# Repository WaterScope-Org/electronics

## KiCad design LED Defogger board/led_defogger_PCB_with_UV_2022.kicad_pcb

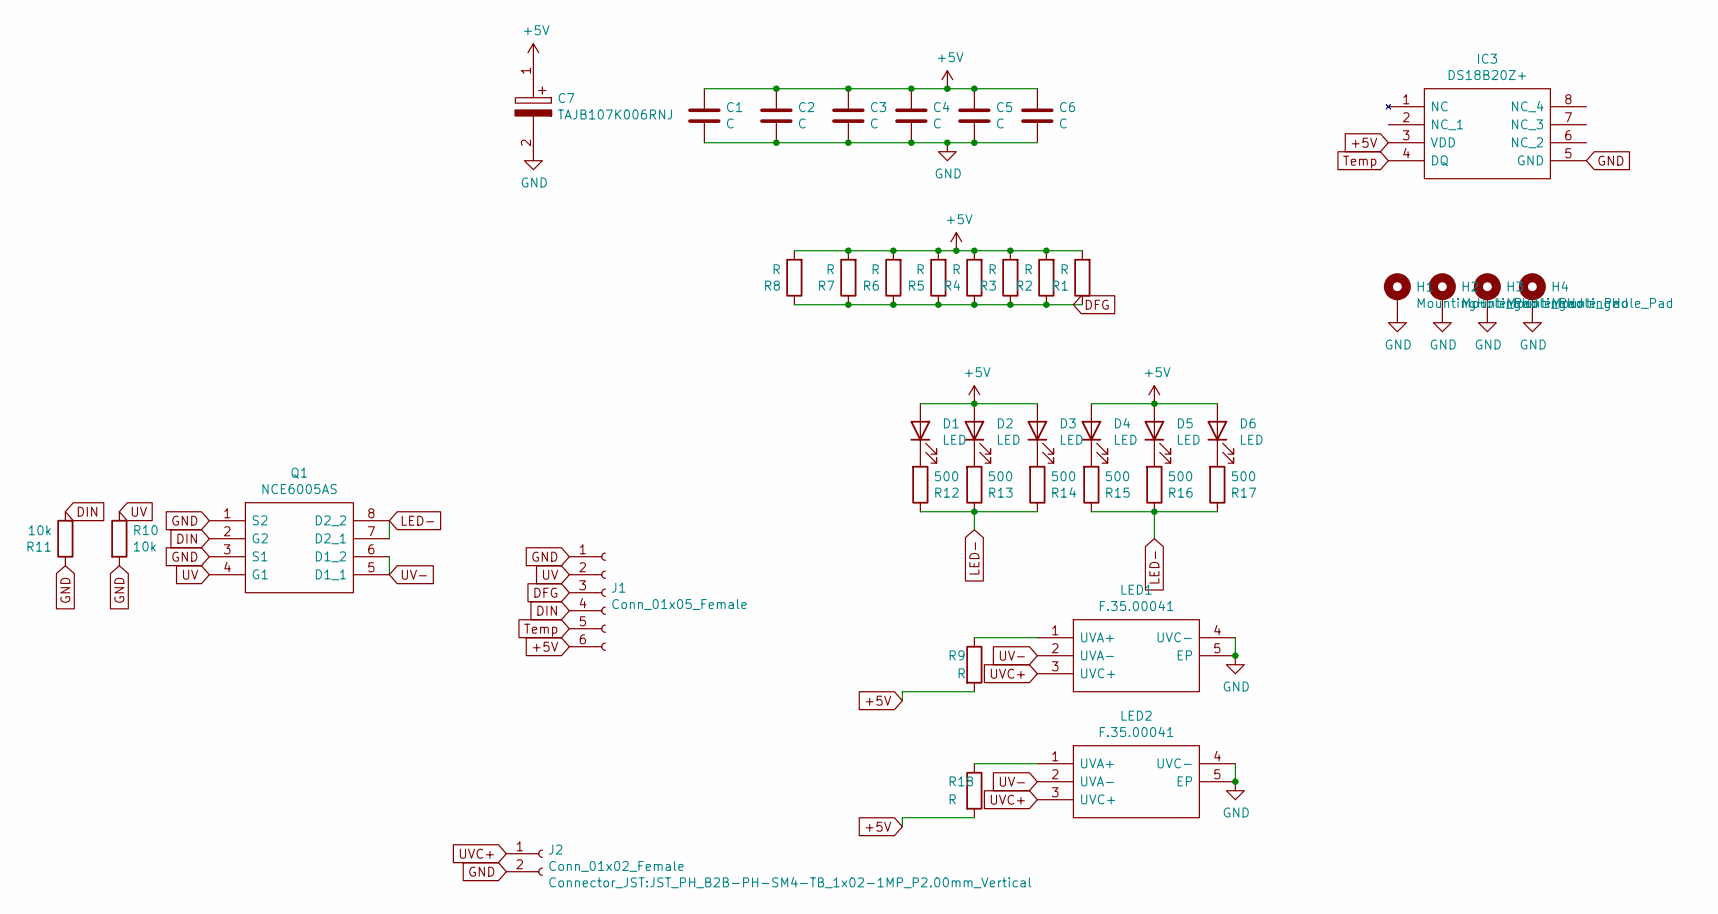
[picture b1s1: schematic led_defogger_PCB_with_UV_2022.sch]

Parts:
C1, C2, C3, C4, C5, C6: C; C_0805_2012Metric_Pad1.15x1.40mm_HandSolder
C7: TAJB107K006RNJ; CAPPM3528X210N; Manufacturer_Part_Number TAJB107K006RNJ; Mouser Part Number 581-TAJB107K006R
D1, D2, D3, D4, D5, D6: LED; LED_0603_1608Metric_Pad1.05x0.95mm_HandSolder
H1, H2, H3, H4: MountingHole_Pad; MountingHole_2.2mm_M2_DIN965_Pad
IC3: DS18B20Z+; SOIC127P600X175-8N; Manufacturer_Part_Number DS18B20Z+
J1: Conn_01x05_Female; JST_PH_B6B-PH-SM4-TB_1x06-1MP_P2.00mm_Vertical
J2: Conn_01x02_Female; JST_PH_B2B-PH-SM4-TB_1x02-1MP_P2.00mm_Vertical
LED1, LED2: F.35.00041; F3500041; Manufacturer_Part_Number F.35.00041
Q1: NCE6005AS; SOIC127P600X175-8N; Manufacturer_Part_Number NCE6005AS
R1, R2, R3, R4, R5, R6, R7, R8: R; R_1210_3225Metric_Pad1.42x2.65mm_HandSolder
R9, R18: R; R_1206_3216Metric_Pad1.30x1.75mm_HandSolder
R10, R11: 10k; R_0805_2012Metric_Pad1.15x1.40mm_HandSolder
R12, R13, R14, R15, R16, R17: 500; R_0805_2012Metric_Pad1.15x1.40mm_HandSolder

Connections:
+5V: C1.1, C2.1, C3.1, C4.1, C5.1, C6.1, C7.1, D1.2 (A), D2.2 (A), D3.2 (A), D4.2 (A), D5.2 (A), D6.2 (A), IC3.3 (VDD), J1.6, R1.2, R2.2, R3.2, R4.2, R5.2, R6.2, R7.2, R8.2, R9.2, R18.2
DFG: J1.3, R1.1, R2.1, R3.1, R4.1, R5.1, R6.1, R7.1, R8.1
DIN: J1.4, Q1.2 (G2), R11.2
GND: C1.2, C2.2, C3.2, C4.2, C5.2, C6.2, C7.2, H1.1, H2.1, H3.1, H4.1, IC3.5 (GND), J1.1, J2.2, LED1.4 (UVC-), LED1.5 (EP), LED2.4 (UVC-), LED2.5 (EP), Q1.1 (S2), Q1.3 (S1), R10.2, R11.1
LED-: Q1.7 (D2_1), Q1.8 (D2_2), R12.1, R13.1, R14.1, R15.1, R16.1, R17.1
unnamed: D1.1 (K), R12.2
unnamed: D2.1 (K), R13.2
unnamed: D3.1 (K), R14.2
unnamed: D4.1 (K), R15.2
unnamed: D5.1 (K), R16.2
unnamed: D6.1 (K), R17.2
unnamed: LED1.1 (UVA+), R9.1
unnamed: LED2.1 (UVA+), R18.1
Temp: IC3.4 (DQ), J1.5
UV: J1.2, Q1.4 (G1), R10.1
UV-: LED1.2 (UVA-), LED2.2 (UVA-), Q1.5 (D1_1), Q1.6 (D1_2)
UVC+: J2.1, LED1.3 (UVC+), LED2.3 (UVC+)

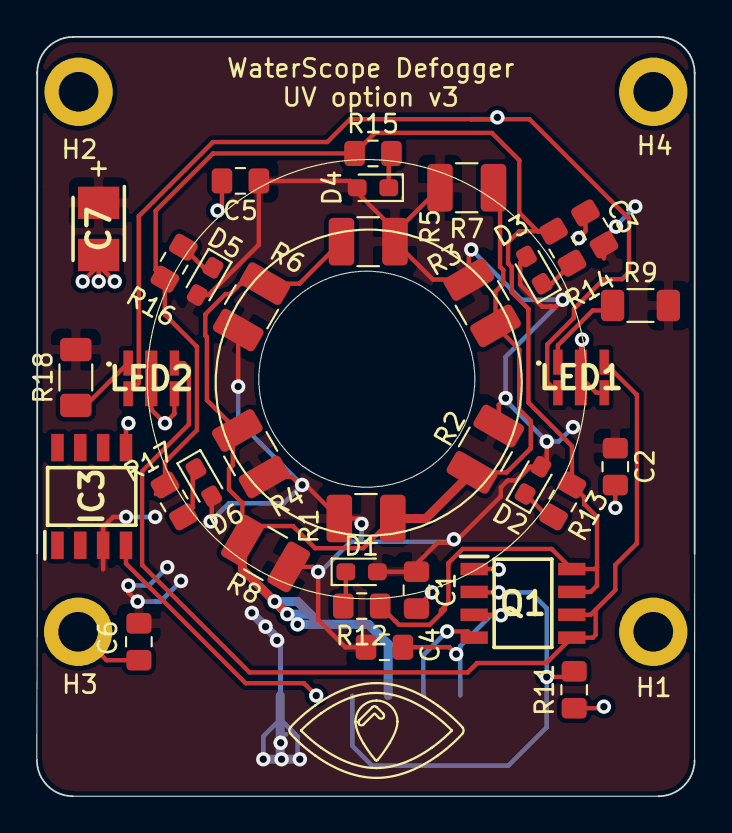
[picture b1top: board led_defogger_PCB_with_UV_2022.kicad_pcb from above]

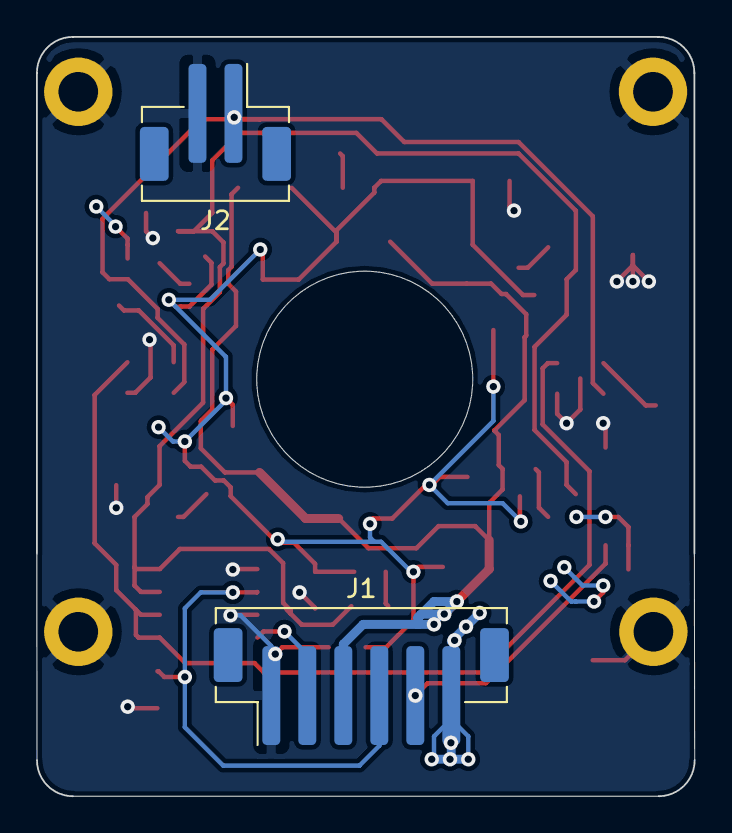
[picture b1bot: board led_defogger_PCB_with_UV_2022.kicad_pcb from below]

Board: 2 copper layers, 36.5 x 42.2 mm, 40 parts (2 on the bottom side), 17 nets.

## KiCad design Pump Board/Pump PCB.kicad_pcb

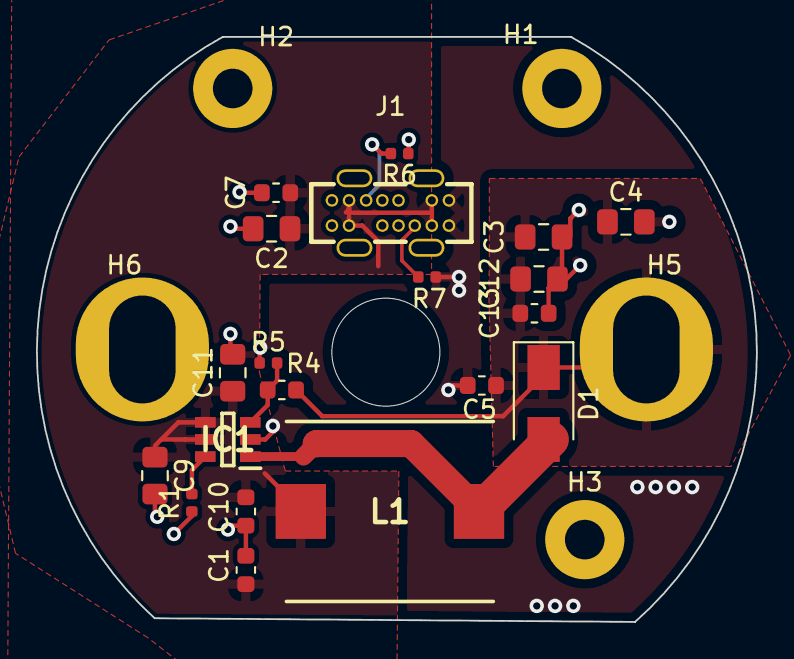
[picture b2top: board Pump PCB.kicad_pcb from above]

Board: 2 copper layers, 40.0 x 32.5 mm, 25 parts (0 on the bottom side), 8 nets.

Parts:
C1, C5, C7, C10, C13: 0.1uF; C_0603_1608Metric
C2, C3, C4, C9, C11, C12: 20uF; C_0805_2012Metric_Pad1.15x1.40mm_HandSolder
D1: D_Schottky; D_SMA
H1, H2, H3: MountingHole; MountingHole_2.2mm_M2_Pad
H5, H6: MountingHole_Pad; MountingHole_3.7mm_Pad
IC1: FP6291; SOT95P280X145-6N
J1: USB-C-TH_TYPE-C-USB-14P
L1: SMMS1040-3R3M; INDPM115100X400N
R1, R5: 10K; R_0402_1005Metric
R4: 190K; R_0603_1608Metric
R6: 5.1k; R_0402_1005Metric
R7: 5.1K; R_0402_1005Metric

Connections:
5V: C1.1, C2.1, C7.1, C9.1, C10.1, C11.1, IC1.4, IC1.5, J1.2, J1.6, J1.9, J1.13, L1.1
12V: C3.1, C4.1, C5.1, C12.1, C13.1, D1.1, H5.1, R4.2
GND: C1.2, C2.2, C3.2, C4.2, C5.2, C7.2, C9.2, C10.2, C11.2, C12.2, C13.2, H6.1, IC1.2, J1.1, J1.7, J1.8, J1.14, R1.2, R5.1, R6.1, R7.2
unnamed: D1.2, IC1.1, L1.2
unnamed: IC1.3, R4.1, R5.2
unnamed: IC1.6, R1.1
unnamed: J1.5, R7.1
unnamed: J1.12, R6.2

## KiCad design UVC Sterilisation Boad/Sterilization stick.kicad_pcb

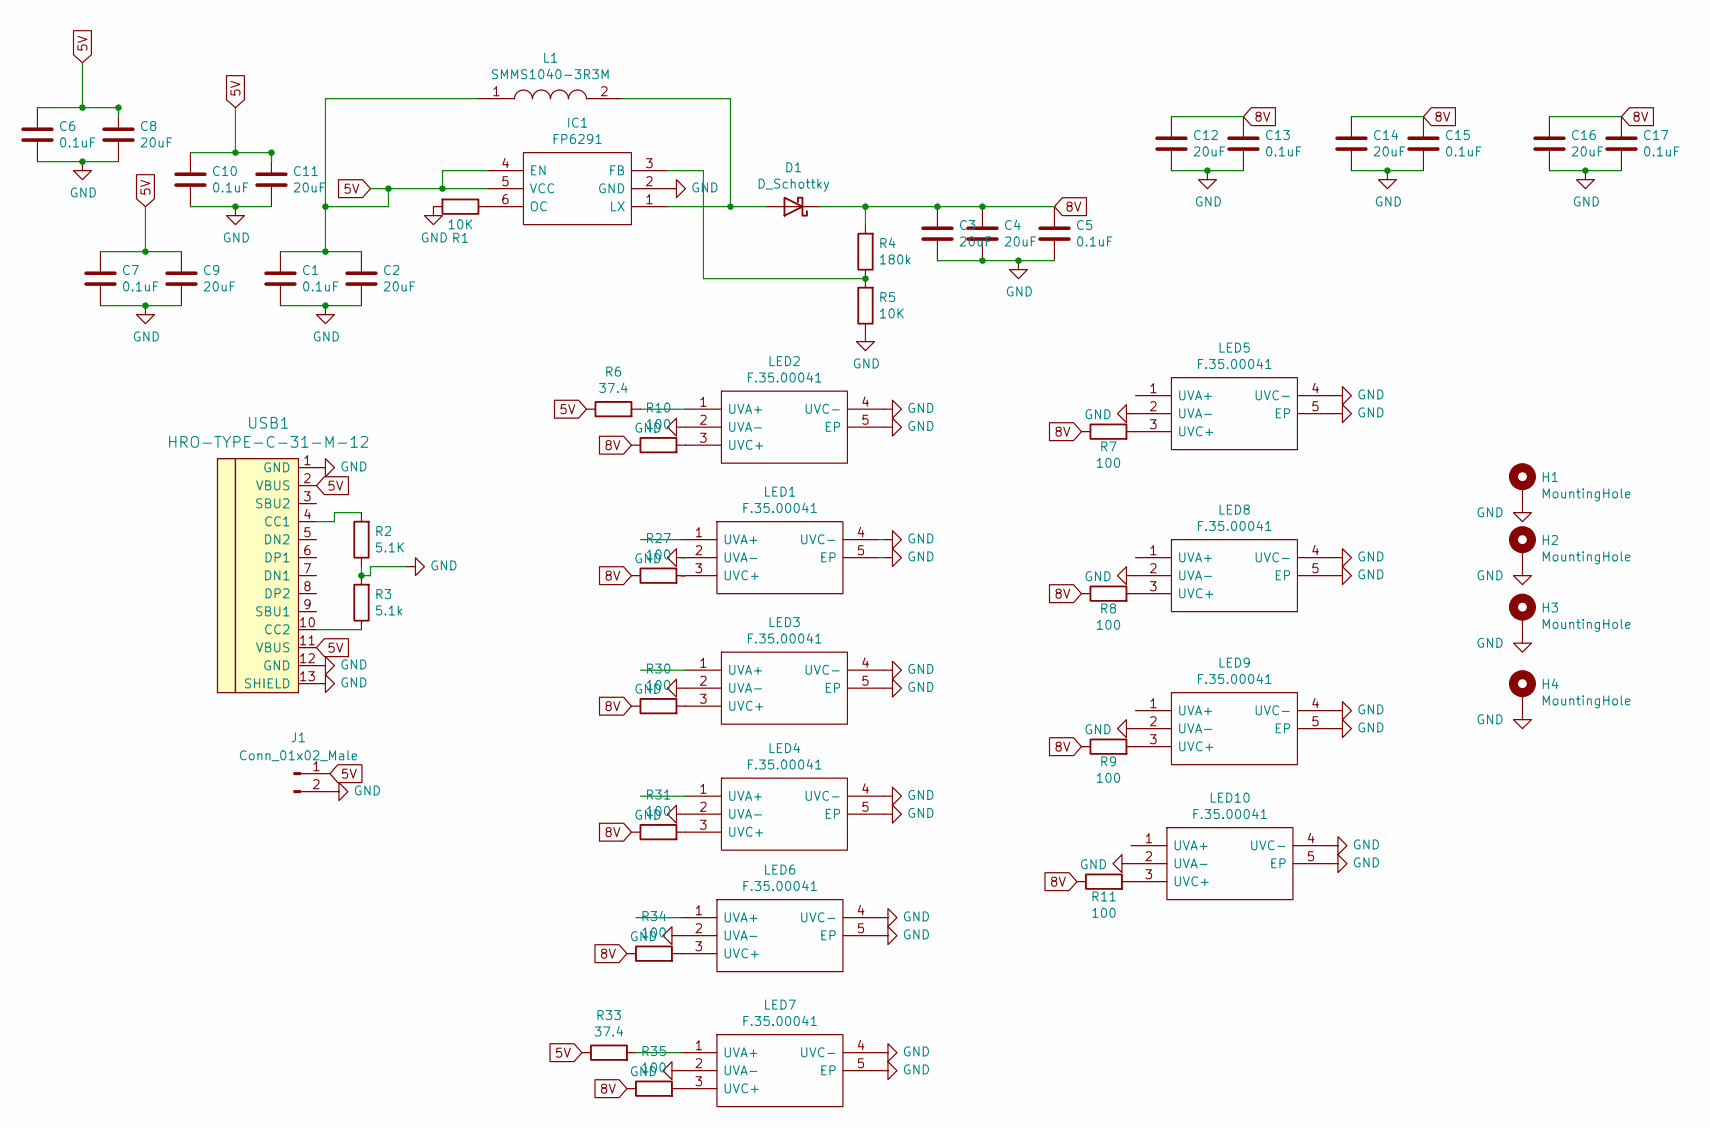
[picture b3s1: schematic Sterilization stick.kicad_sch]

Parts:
C1, C5, C6, C7, C10, C13, C15, C17: 0.1uF; C_0603_1608Metric; LCSC Part C14663
C2, C3, C4, C8, C9, C11, C12, C14, C16: 20uF; C_0805_2012Metric_Pad1.15x1.40mm_HandSolder; LCSC Part C45783
D1: D_Schottky; D_SMA; LCSC Part C383313
H1, H2, H3, H4: MountingHole; MountingHole_4.3mm_M4_DIN965_Pad
IC1: FP6291; SOT95P280X145-6N; Manufacturer_Part_Number FP6291; LCSC Part C18701
J1: Conn_01x02_Male; JST_XH_S2B-XH-A-1_1x02_P2.50mm_Horizontal
L1: SMMS1040-3R3M; INDPM115100X400N; Manufacturer_Part_Number SMMS1040-3R3M; LCSC Part C149592
LED1, LED2, LED3, LED4, LED5, LED6, LED7, LED8, LED9, LED10: F.35.00041; F3500041; Manufacturer_Part_Number F.35.00041; LCSC Part C909692
R1: 10K; R_0402_1005Metric; LCSC Part C25744
R2: 5.1K; R_0402_1005Metric; LCSC Part C25905
R3: 5.1k; R_0402_1005Metric; LCSC Part C25905
R4: 180k; R_0603_1608Metric; LCSC Part C22932
R5: 10K; R_0603_1608Metric_Pad0.98x0.95mm_HandSolder; LCSC Part C25744
R6, R33: 37.4; R_1206_3216Metric; LCSC Part C247280
R7, R8, R9, R10, R11, R27, R30, R31, R34, R35: 100; R_1206_3216Metric; LCSC Part C17901
USB1: HRO-TYPE-C-31-M-12; HRO-TYPE-C-31-M-12-HandSoldering

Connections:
5V: C1.1, C2.1, C6.1, C7.1, C8.1, C9.1, C10.1, C11.1, IC1.4 (EN), IC1.5 (VCC), J1.1, L1.1, R6.1, R33.1, USB1.2 (VBUS), USB1.11 (VBUS)
8V: C3.1, C4.1, C5.1, C12.1, C13.1, C14.1, C15.1, C16.1, C17.1, D1.1 (K), R4.2, R7.1, R8.1, R9.1, R10.1, R11.1, R27.1, R30.1, R31.1, R34.1, R35.1
GND: C1.2, C2.2, C3.2, C4.2, C5.2, C6.2, C7.2, C8.2, C9.2, C10.2, C11.2, C12.2, C13.2, C14.2, C15.2, C16.2, C17.2, H1.1, H2.1, H3.1, H4.1, IC1.2 (GND), J1.2, LED1.2 (UVA-), LED1.4 (UVC-), LED1.5 (EP), LED2.2 (UVA-), LED2.4 (UVC-), LED2.5 (EP), LED3.2 (UVA-), LED3.4 (UVC-), LED3.5 (EP), LED4.2 (UVA-), LED4.4 (UVC-), LED4.5 (EP), LED5.2 (UVA-), LED5.4 (UVC-), LED5.5 (EP), LED6.2 (UVA-), LED6.4 (UVC-), LED6.5 (EP), LED7.2 (UVA-), LED7.4 (UVC-), LED7.5 (EP), LED8.2 (UVA-), LED8.4 (UVC-), LED8.5 (EP), LED9.2 (UVA-), LED9.4 (UVC-), LED9.5 (EP), LED10.2 (UVA-), LED10.4 (UVC-), LED10.5 (EP), R1.2, R2.1, R3.2, R5.1, USB1.1 (GND), USB1.12 (GND), USB1.13 (SHIELD)
unnamed: D1.2 (A), IC1.1 (LX), L1.2
unnamed: IC1.3 (FB), R4.1, R5.2
unnamed: IC1.6 (OC), R1.1
unnamed: LED1.3 (UVC+), R27.2
unnamed: LED2.1 (UVA+), R6.2
unnamed: LED2.3 (UVC+), R10.2
unnamed: LED3.3 (UVC+), R30.2
unnamed: LED4.3 (UVC+), R31.2
unnamed: LED5.3 (UVC+), R7.2
unnamed: LED6.3 (UVC+), R34.2
unnamed: LED7.1 (UVA+), R33.2
unnamed: LED7.3 (UVC+), R35.2
unnamed: LED8.3 (UVC+), R8.2
unnamed: LED9.3 (UVC+), R9.2
unnamed: LED10.3 (UVC+), R11.2
unnamed: R2.2, USB1.4 (CC1)
unnamed: R3.1, USB1.10 (CC2)

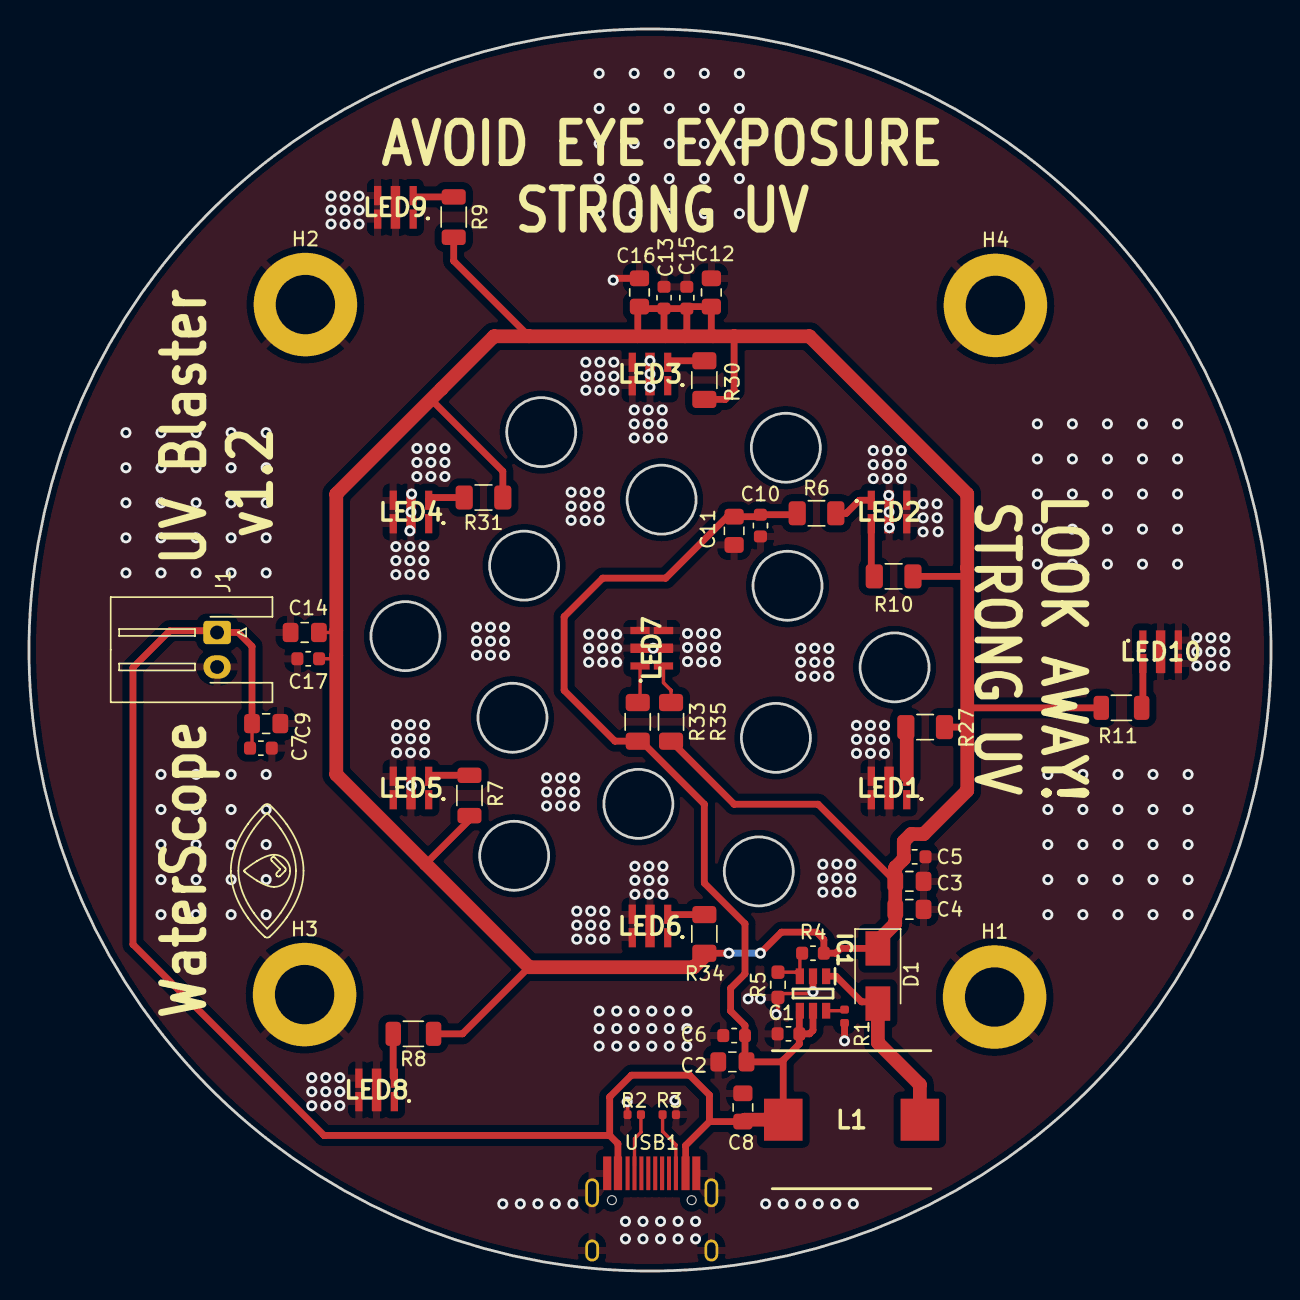
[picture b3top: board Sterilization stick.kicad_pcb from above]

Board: 2 copper layers, 90.0 x 90.0 mm, 53 parts (0 on the bottom side), 20 nets.

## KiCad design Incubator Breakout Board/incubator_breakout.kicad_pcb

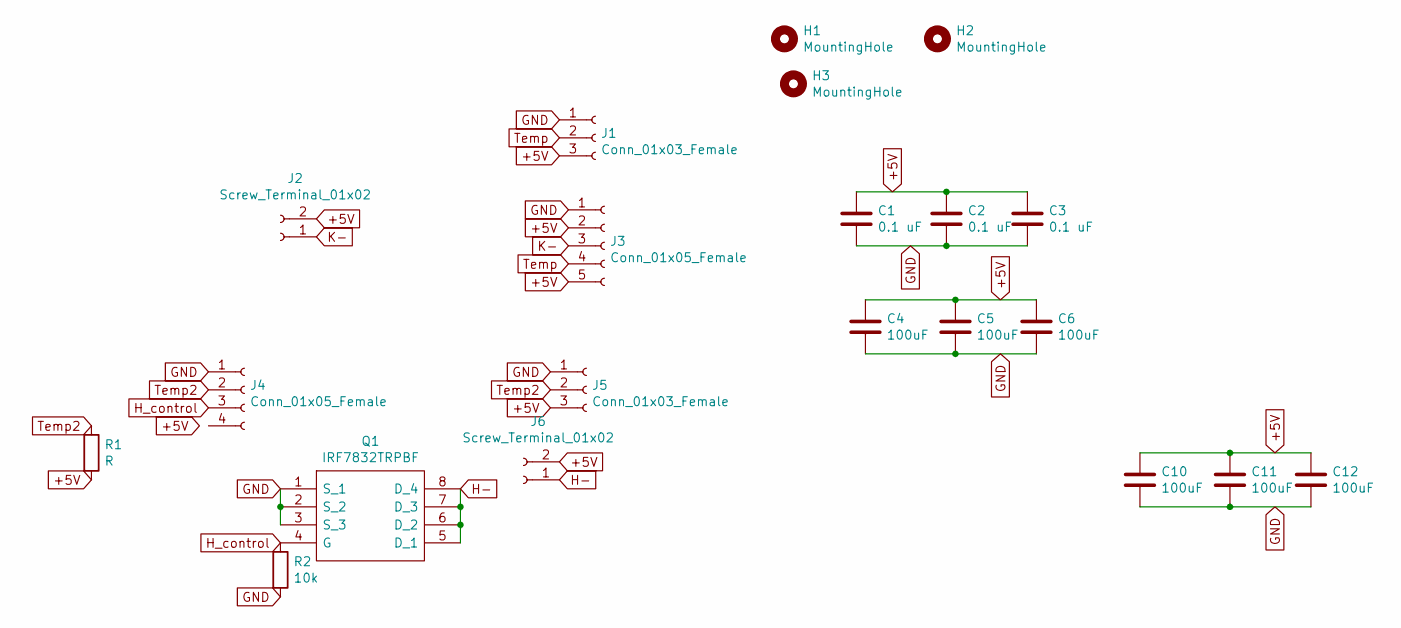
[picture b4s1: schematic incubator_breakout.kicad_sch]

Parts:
C1, C2, C3: 0.1 uF; C_0805_2012Metric_Pad1.15x1.40mm_HandSolder
C4, C5, C6: 100uF; C_0805_2012Metric_Pad1.15x1.40mm_HandSolder
C10, C11, C12: 100uF; C_0805_2012Metric_Pad1.18x1.45mm_HandSolder
H1, H2, H3: MountingHole; MountingHole_2.2mm_M2_Pad
J1, J5: Conn_01x03_Female; JST_PH_S3B-PH-K_1x03_P2.00mm_Horizontal
J2, J6: Screw_Terminal_01x02; JST_XH_S2B-XH-A_1x02_P2.50mm_Horizontal
J3: Conn_01x05_Female; JST_PH_S5B-PH-K_1x05_P2.00mm_Horizontal
J4: Conn_01x05_Female; JST_PH_S4B-PH-K_1x04_P2.00mm_Horizontal
Q1: IRF7832TRPBF; SOIC127P600X175-8N; Manufacturer_Part_Number NTMS4807NR2G; Mouser Part Number 863-NTMS4807NR2G
R1: R; R_0402_1005Metric
R2: 10k; R_0805_2012Metric_Pad1.15x1.40mm_HandSolder

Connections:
+5V: C1.1, C2.1, C3.1, C4.1, C5.1, C6.1, C10.1, C11.1, C12.1, J1.3, J2.2, J3.2, J3.5, J5.3, J6.2, R1.2
GND: C1.2, C2.2, C3.2, C4.2, C5.2, C6.2, C10.2, C11.2, C12.2, J1.1, J3.1, J4.1, J5.1, Q1.1 (S_1), Q1.2 (S_2), Q1.3 (S_3), R2.2
H-: J6.1, Q1.5 (D_1), Q1.6 (D_2), Q1.7 (D_3), Q1.8 (D_4)
H_control: J4.3, Q1.4 (G), R2.1
K-: J2.1, J3.3
Temp: J1.2, J3.4
Temp2: J4.2, J5.2, R1.1

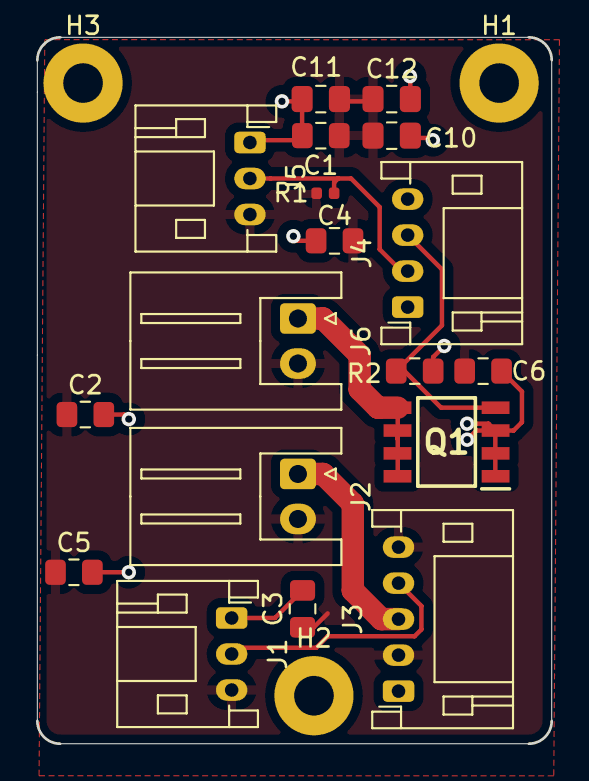
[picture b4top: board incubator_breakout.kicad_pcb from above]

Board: 2 copper layers, 28.6 x 39.2 mm, 21 parts (0 on the bottom side), 7 nets.

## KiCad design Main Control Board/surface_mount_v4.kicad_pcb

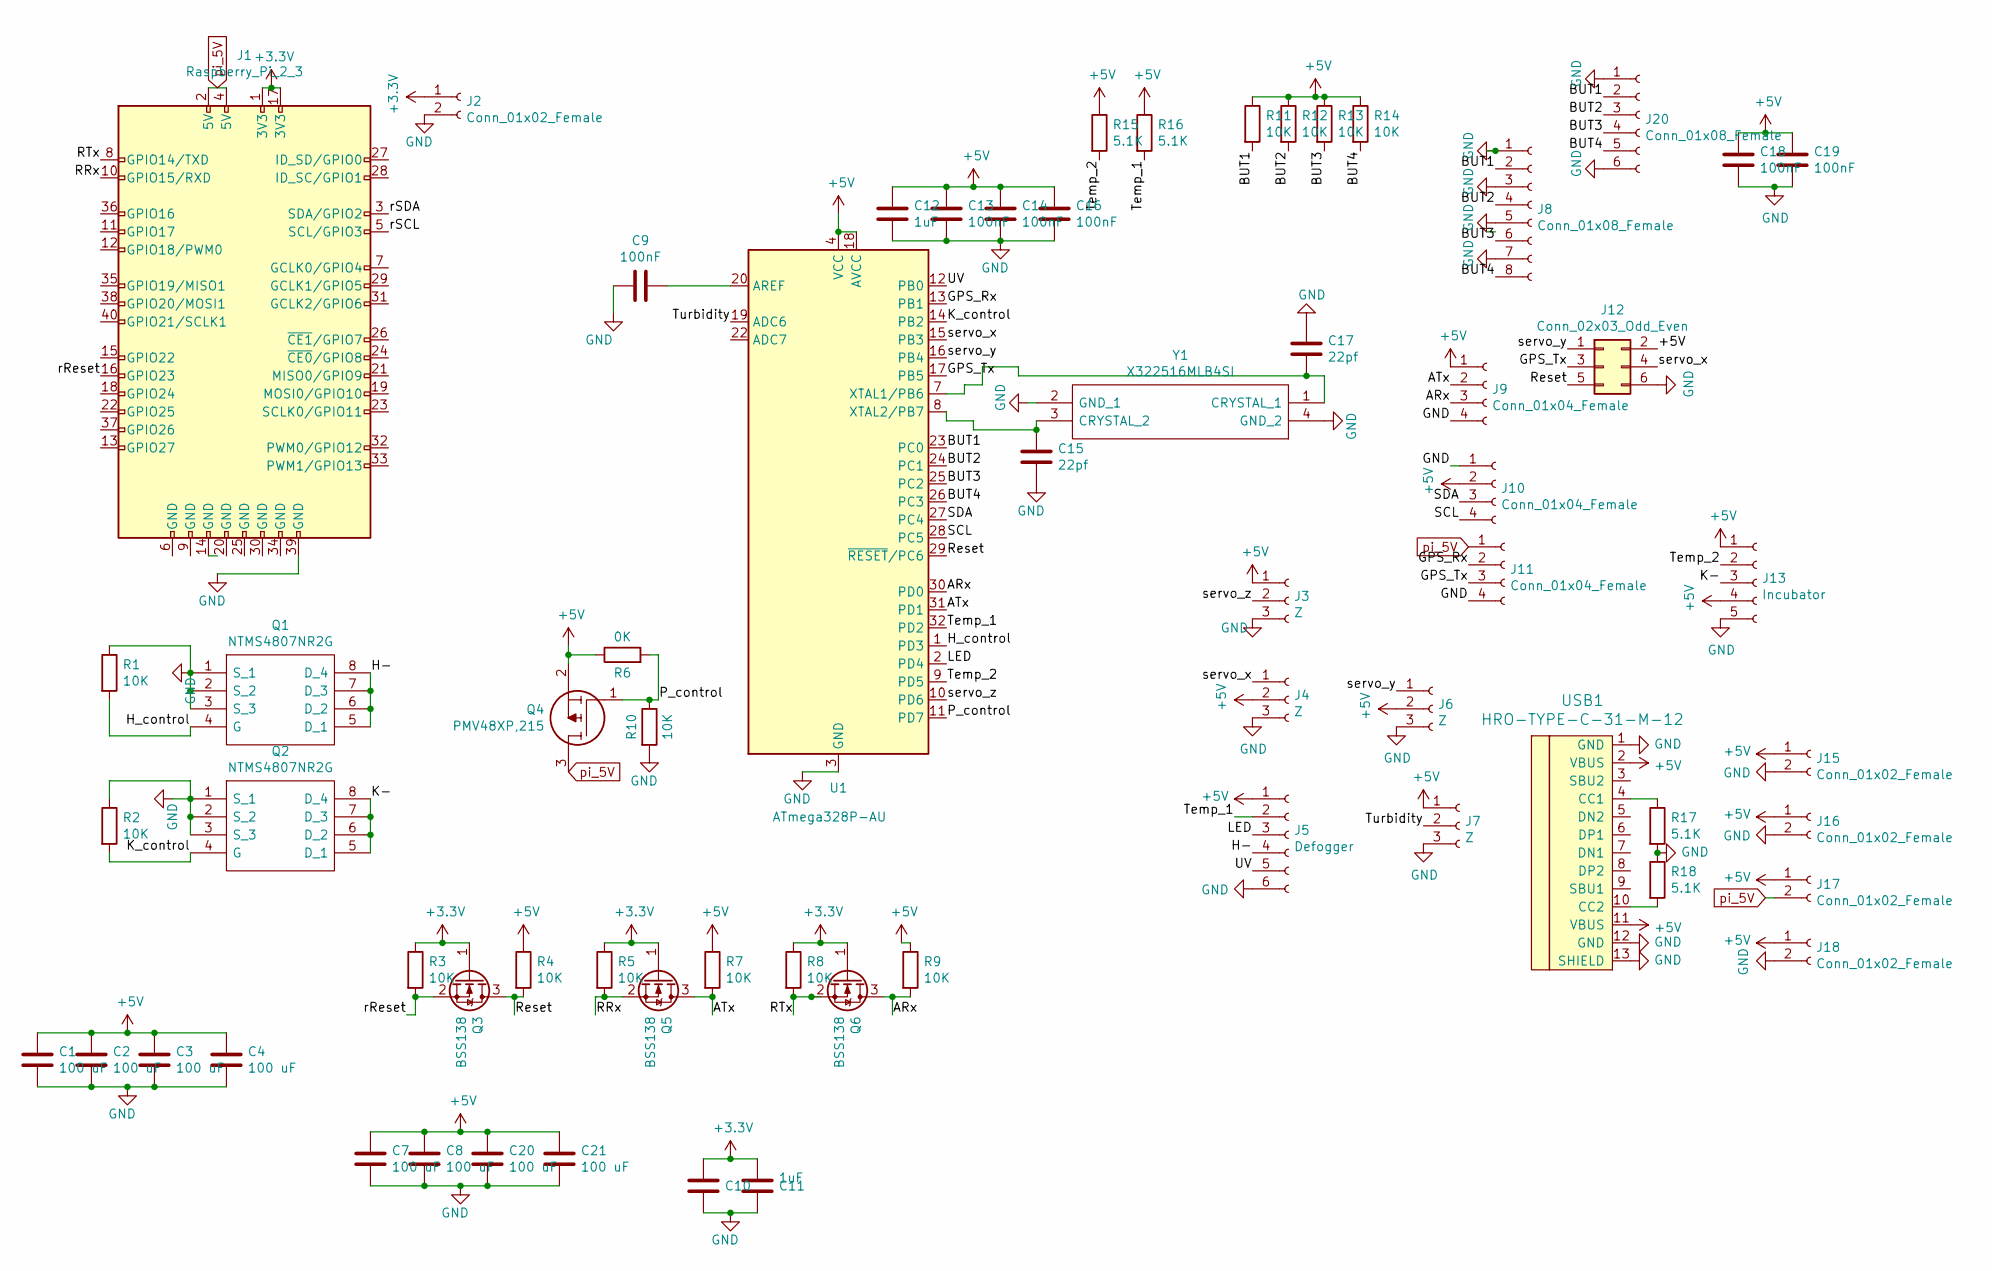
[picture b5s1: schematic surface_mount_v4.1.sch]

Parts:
C1, C2, C3, C4, C7, C8, C20, C21: 100 uF; R_1206_3216Metric; LCSC Part C15008
C9, C10, C13, C14, C16, C18, C19: 100nF; C_0603_1608Metric
C11, C12: 1uF; C_0603_1608Metric
C15, C17: 22pf; C_0603_1608Metric_Pad1.05x0.95mm_HandSolder; LCSC Part C1653
J1: Raspberry_Pi_2_3; PinSocket_2x20_P2.54mm_Vertical_SMD
J2, J17: Conn_01x02_Female; PinHeader_1x02_P2.54mm_Vertical
J3, J7: Z; JST_PH_B3B-PH-SM4-TB_1x03-1MP_P2.00mm_Vertical
J4, J6: Z; PinHeader_1x03_P2.54mm_Vertical
J5: Defogger; JST_PH_S6B-PH-SM4-TB_1x06-1MP_P2.00mm_Horizontal
J8: Conn_01x08_Female; JST_PH_S8B-PH-SM4-TB_1x08-1MP_P2.00mm_Horizontal
J9: Conn_01x04_Female; PinHeader_1x04_P2.54mm_Vertical
J10, J11: Conn_01x04_Female; JST_PH_B4B-PH-SM4-TB_1x04-1MP_P2.00mm_Vertical
J12: Conn_02x03_Odd_Even; PinHeader_2x03_P2.54mm_Vertical
J13: Incubator; JST_PH_S5B-PH-SM4-TB_1x05-1MP_P2.00mm_Horizontal
J15, J16, J18: Conn_01x02_Female; JST_XH_B2B-XH-A_1x02_P2.50mm_Vertical
J20: Conn_01x08_Female; 06FEBTVKN
Q1, Q2: NTMS4807NR2G; SOIC127P600X175-8N; Manufacturer_Part_Number NTMS4807NR2G; Mouser Part Number 863-NTMS4807NR2G
Q3, Q5, Q6: BSS138; SOT-23
Q4: PMV48XP,215; SOT95P230X110-3N; Manufacturer_Part_Number PMV48XP,215; Mouser Part Number 771-PMV48XP215
R1, R2, R3, R4, R5, R7, R8, R9, R10, R11, R12, R13, R14: 10K; R_0402_1005Metric
R6: 0K; R_0805_2012Metric_Pad1.15x1.40mm_HandSolder
R15, R16, R17, R18: 5.1K; R_0402_1005Metric
U1: ATmega328P-AU; TQFP-32_7x7mm_P0.8mm
USB1: HRO-TYPE-C-31-M-12; HRO-TYPE-C-31-M-12-Assembly
Y1: X322516MLB4SI; Manufacturer_Part_Number X322516MLB4SI

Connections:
+3V3: C10.1, C11.2, J1.1 (3V3), J1.17 (3V3), J2.1, Q3.1 (G), Q5.1 (G), Q6.1 (G), R3.1, R5.1, R8.1
+5V: C1.1, C2.1, C3.1, C4.1, C7.1, C8.1, C12.1, C13.1, C14.1, C16.1, C18.1, C19.1, C20.1, C21.1, J3.1, J4.2, J5.1, J6.2, J7.1, J9.1, J10.2, J12.2, J13.1, J13.4, J15.1, J16.1, J17.1, J18.1, Q4.2, R4.1, R6.1, R7.1, R9.1, R11.1, R12.1, R13.1, R14.1, R15.1, R16.1, U1.4 (VCC), U1.6 (VCC), U1.18 (AVCC), USB1.2 (VBUS), USB1.11 (VBUS)
/ARx: J9.3, Q6.3 (D), R9.2, U1.30 (PD0)
/ATx: J9.2, Q5.3 (D), R7.2, U1.31 (PD1)
/BUT1: J8.2, J20.2, R11.2, U1.23 (PC0)
/BUT2: J8.4, J20.3, R12.2, U1.24 (PC1)
/BUT3: J8.6, J20.4, R13.2, U1.25 (PC2)
/BUT4: J8.8, J20.5, R14.2, U1.26 (PC3)
/GPS_Rx: J11.2, U1.13 (PB1)
/GPS_Tx: J11.3, J12.3, U1.17 (PB5)
/H-: J5.4, Q1.5 (D_1), Q1.6 (D_2), Q1.7 (D_3), Q1.8 (D_4)
/H_control: Q1.4 (G), R1.2, U1.1 (PD3)
/K-: J13.3, Q2.5 (D_1), Q2.6 (D_2), Q2.7 (D_3), Q2.8 (D_4)
/K_control: Q2.4 (G), R2.2, U1.14 (PB2)
/LED: J5.3, U1.2 (PD4)
/P_control: Q4.1, R6.2, R10.1, U1.11 (PD7)
/RRx: J1.10 (GPIO15/RXD), Q5.2 (S), R5.2
/RTx: J1.8 (GPIO14/TXD), Q6.2 (S), R8.2
/Reset: J12.5, Q3.3 (D), R4.2, U1.29 (~RESET~/PC6)
/SCL: J10.4, U1.28 (PC5)
/SDA: J10.3, U1.27 (PC4)
/Temp_1: J5.2, R16.2, U1.32 (PD2)
/Temp_2: J13.2, R15.2, U1.9 (PD5)
/Turbidity: J7.2, U1.19 (ADC6)
/UV: J5.5, U1.12 (PB0)
/rReset: J1.16 (GPIO23), Q3.2 (S), R3.2
/rSCL: J1.5 (SCL/GPIO3)
/rSDA: J1.3 (SDA/GPIO2)
/servo_x: J4.1, J12.4, U1.15 (PB3)
/servo_y: J6.1, J12.1, U1.16 (PB4)
/servo_z: J3.2, U1.10 (PD6)
GND: C1.2, C2.2, C3.2, C4.2, C7.2, C8.2, C9.2, C10.2, C11.1, C12.2, C13.2, C14.2, C15.2, C16.2, C17.1, C18.2, C19.2, C20.2, C21.2, J1.39 (GND), J2.2, J3.3, J4.3, J5.6, J6.3, J7.3, J8.1, J8.3, J8.5, J8.7, J9.4, J10.1, J11.4, J12.6, J13.5, J15.2, J16.2, J18.2, J20.1, J20.6, Q1.1 (S_1), Q1.2 (S_2), Q1.3 (S_3), Q2.1 (S_1), Q2.2 (S_2), Q2.3 (S_3), R1.1, R2.1, R10.2, R17.2, R18.1, U1.3 (GND), U1.5 (GND), U1.21 (GND), USB1.1 (GND), USB1.12 (GND), USB1.13 (SHIELD), Y1.2 (GND_1), Y1.4 (GND_2)
unnamed: C9.1, U1.20 (AREF)
unnamed: C15.1, U1.8 (XTAL2/PB7), Y1.3 (CRYSTAL_2)
unnamed: C17.2, U1.7 (XTAL1/PB6), Y1.1 (CRYSTAL_1)
unnamed: R17.1, USB1.4 (CC1)
unnamed: R18.2, USB1.10 (CC2)
pi_5V: J1.2 (5V), J1.4 (5V), J11.1, J17.2, Q4.3

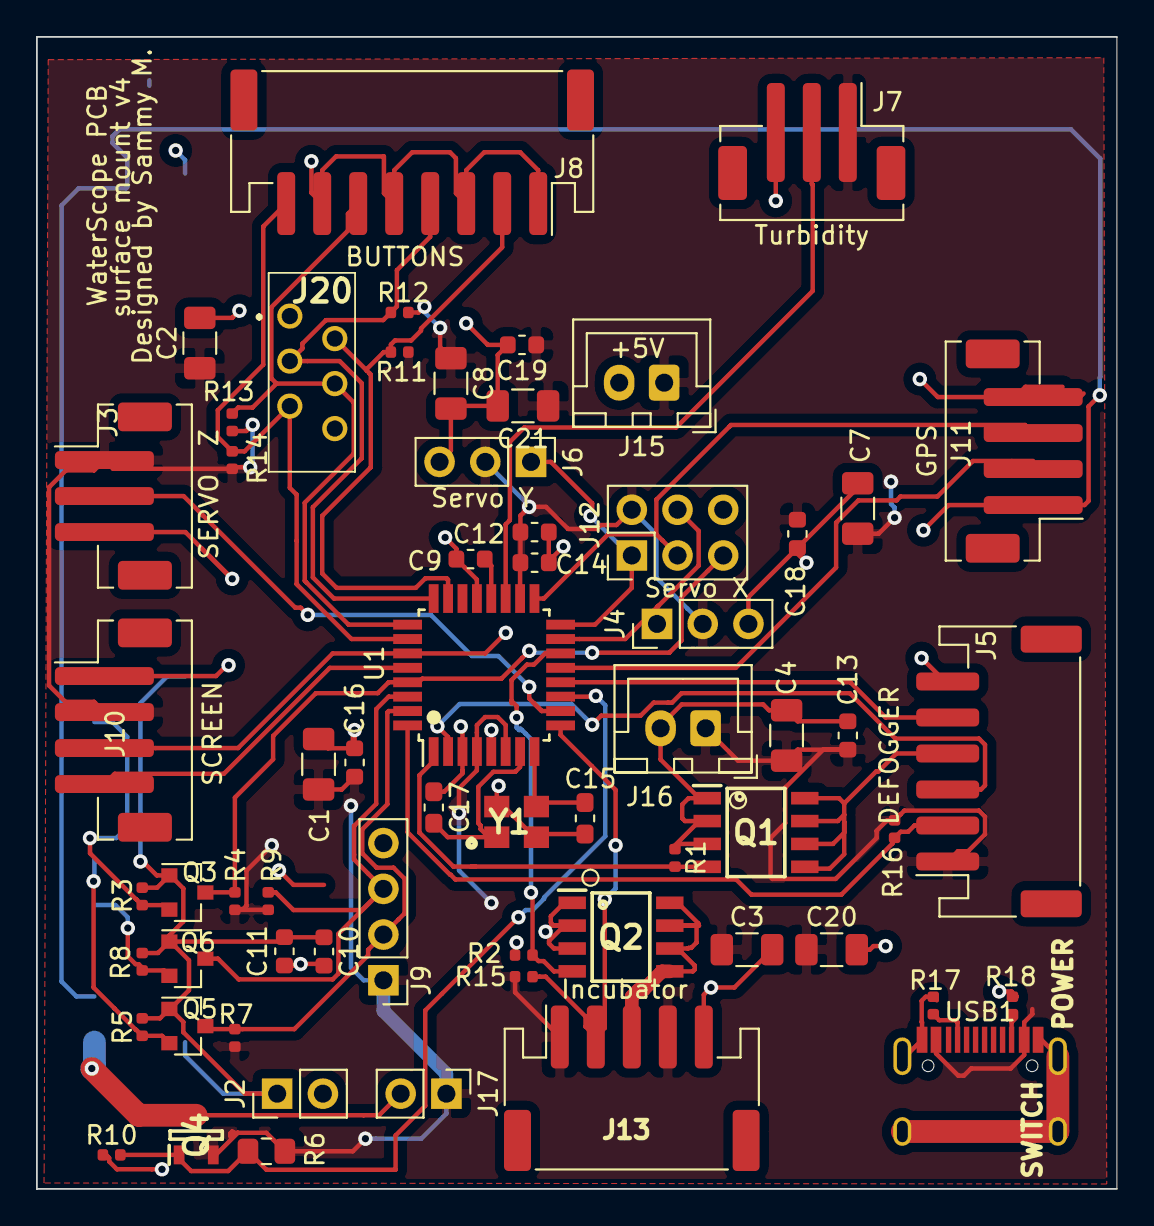
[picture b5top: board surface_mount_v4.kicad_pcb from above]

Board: 2 copper layers, 60.0 x 64.0 mm, 63 parts (1 on the bottom side), 36 nets.

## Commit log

2023-12-29 init commit
